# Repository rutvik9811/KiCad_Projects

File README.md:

# KiCad_Projects
These are PCB design Projects ( this doesn't include any code only contains Schematics and PCB design)

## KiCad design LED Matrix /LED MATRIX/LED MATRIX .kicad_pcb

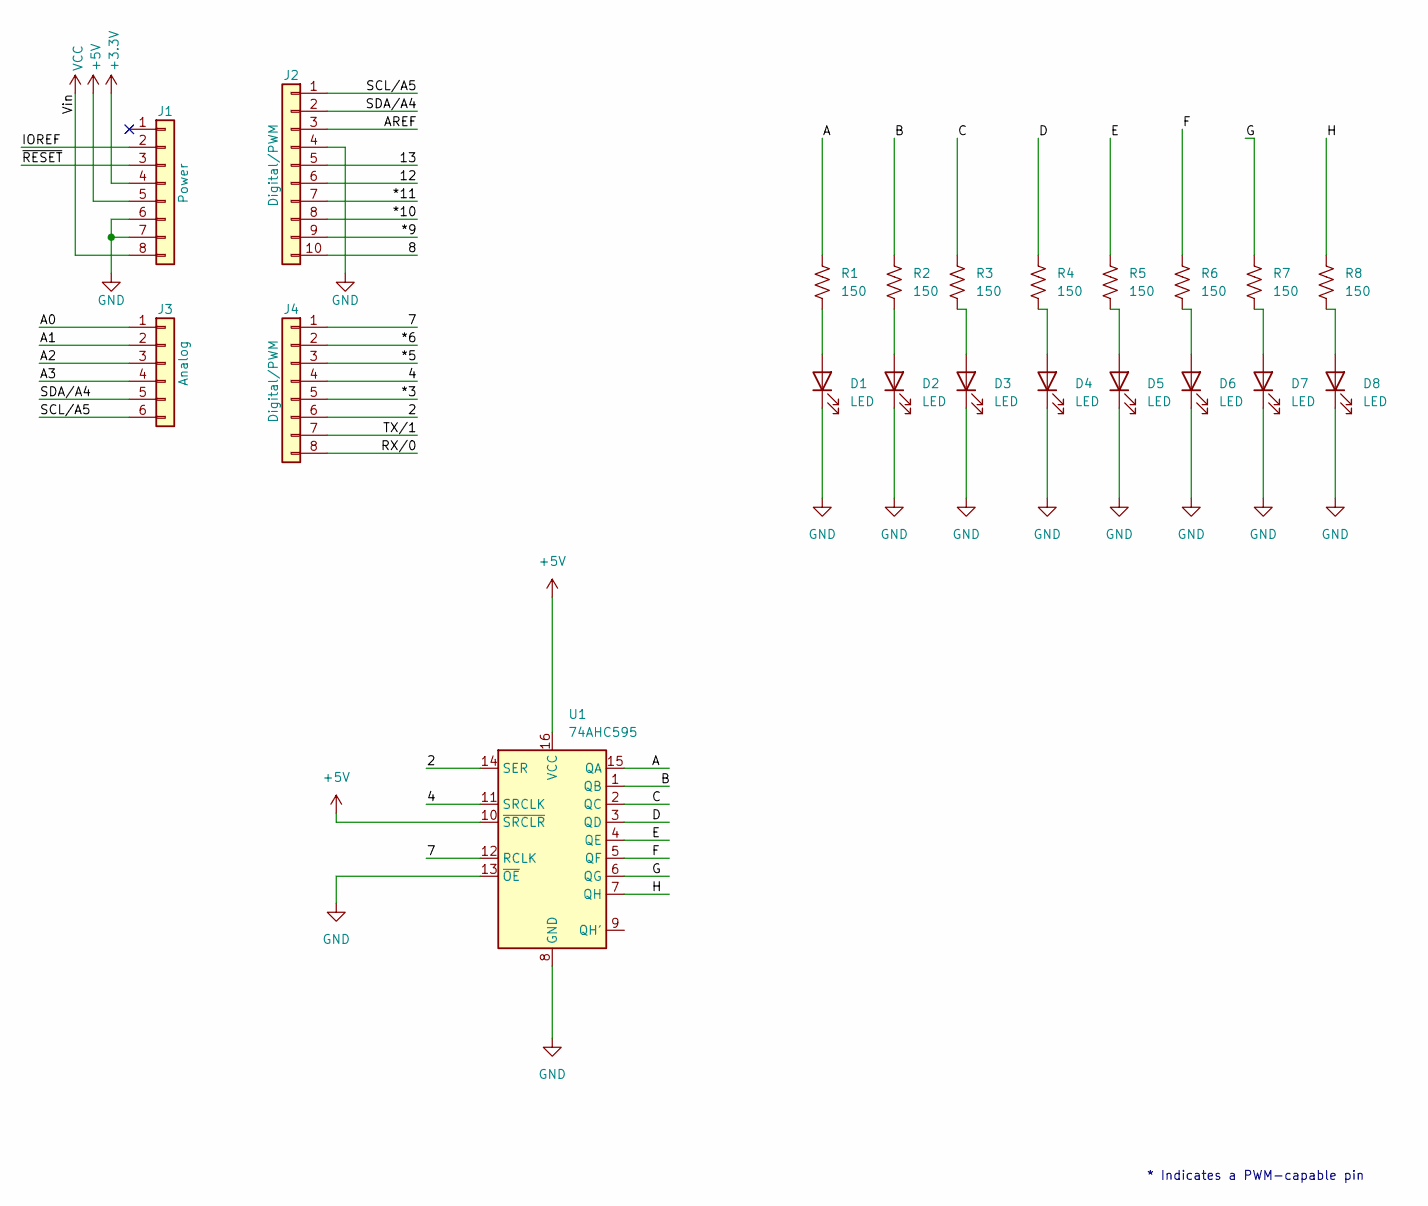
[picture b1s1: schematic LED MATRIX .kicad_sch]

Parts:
D1, D2, D3, D4, D5, D6, D7, D8: LED; LED_D1.8mm_W1.8mm_H2.4mm_Horizontal_O1.27mm_Z1.6mm
J1: Power; PinSocket_1x08_P2.54mm_Vertical
J2: Digital/PWM; PinSocket_1x10_P2.54mm_Vertical
J3: Analog; PinSocket_1x06_P2.54mm_Vertical
J4: Digital/PWM; PinSocket_1x08_P2.54mm_Vertical
R1, R2, R3, R4, R5, R6, R7, R8: 150; R_Axial_DIN0207_L6.3mm_D2.5mm_P10.16mm_Horizontal
U1: 74AHC595; DIP-16_W7.62mm

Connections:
+3V3: J1.4
+5V: J1.5, U1.10 (~SRCLR), U1.16 (VCC)
/2: J4.6, U1.14 (SER)
/4: J4.4, U1.11 (SRCLK)
/7: J4.1, U1.12 (RCLK)
/8: J2.10
/12: J2.6
/13: J2.5
/*3: J4.5
/*5: J4.3
/*6: J4.2
/*9: J2.9
/*10: J2.8
/*11: J2.7
/A: R1.1, U1.15 (QA)
/A0: J3.1
/A1: J3.2
/A2: J3.3
/A3: J3.4
/AREF: J2.3
/B: R2.1, U1.1 (QB)
/C: R3.1, U1.2 (QC)
/D: R4.1, U1.3 (QD)
/E: R5.1, U1.4 (QE)
/F: R6.1, U1.5 (QF)
/G: R7.1, U1.6 (QG)
/H: R8.1, U1.7 (QH)
/IOREF: J1.2
/RX/0: J4.8
/SCL/A5: J2.1, J3.6
/SDA/A4: J2.2, J3.5
/TX/1: J4.7
/~RESET: J1.3
GND: D1.1 (K), D2.1 (K), D3.1 (K), D4.1 (K), D5.1 (K), D6.1 (K), D7.1 (K), D8.1 (K), J1.6, J1.7, J2.4, U1.8 (GND), U1.13 (~OE)
unnamed: D1.2 (A), R1.2
unnamed: D2.2 (A), R2.2
unnamed: D3.2 (A), R3.2
unnamed: D4.2 (A), R4.2
unnamed: D5.2 (A), R5.2
unnamed: D6.2 (A), R6.2
unnamed: D7.2 (A), R7.2
unnamed: D8.2 (A), R8.2
VCC: J1.8

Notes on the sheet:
* Indicates a PWM-capable pin

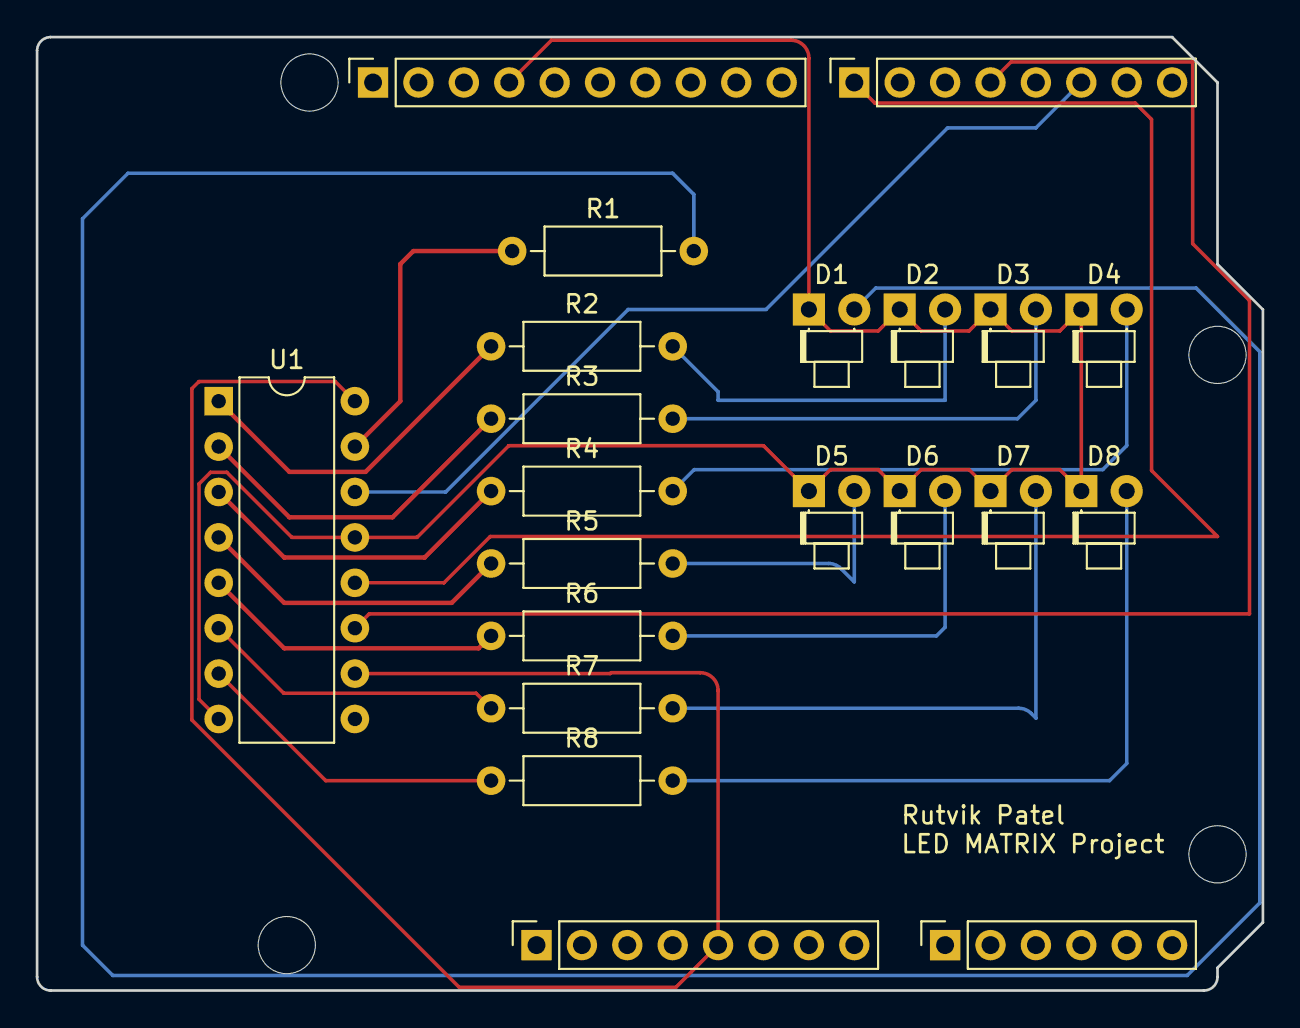
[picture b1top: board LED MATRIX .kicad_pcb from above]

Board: 2 copper layers, 68.6 x 53.3 mm, 25 parts (0 on the bottom side), 23 nets.

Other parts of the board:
MH1, MH2, MH3, MH4: MountingHole_3.2mm

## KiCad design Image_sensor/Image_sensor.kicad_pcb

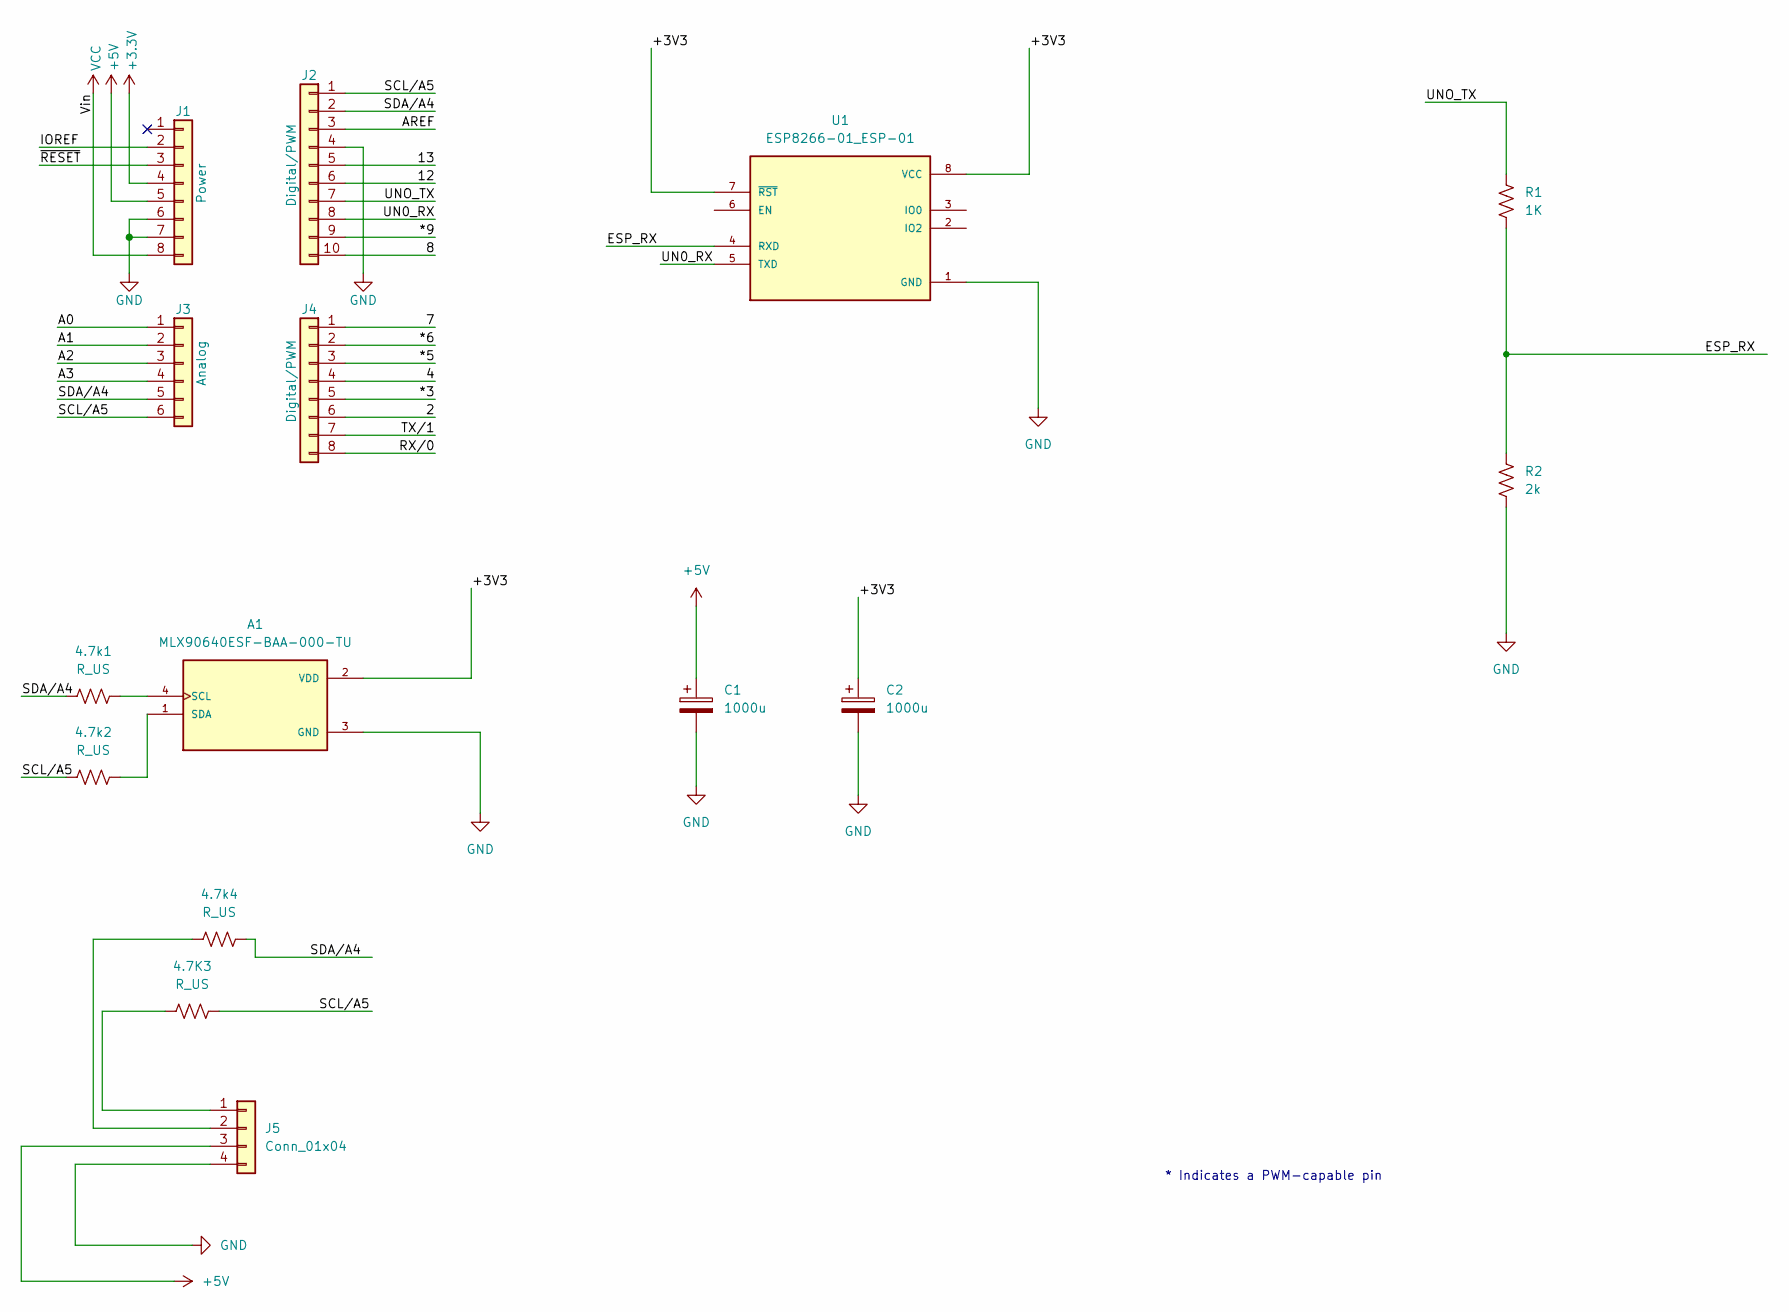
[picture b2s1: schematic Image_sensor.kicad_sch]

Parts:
4.7K3, 4.7k1, 4.7k2, 4.7k4: R_US; R_Axial_DIN0207_L6.3mm_D2.5mm_P10.16mm_Horizontal
A1: MLX90640ESF-BAA-000-TU; TO292P930H600-4; PARTREV 11
C1, C2: 1000u; CP_Radial_D10.0mm_P5.00mm
J1: Power; PinSocket_1x08_P2.54mm_Vertical
J2: Digital/PWM; PinSocket_1x10_P2.54mm_Vertical
J3: Analog; PinSocket_1x06_P2.54mm_Vertical
J4: Digital/PWM; PinSocket_1x08_P2.54mm_Vertical
J5: Conn_01x04; NS-Tech_Grove_1x04_P2mm_Vertical
R1: 1K; R_Axial_DIN0207_L6.3mm_D2.5mm_P10.16mm_Horizontal
R2: 2k; R_Axial_DIN0207_L6.3mm_D2.5mm_P10.16mm_Horizontal
U1: ESP8266-01_ESP-01; XCVR_ESP8266-01_ESP-01; PARTREV V1.2

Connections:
+5V: C1.1, J1.5, J5.3
/2: J4.6
/4: J4.4
/7: J4.1
/8: J2.10
/12: J2.6
/13: J2.5
/*3: J4.5
/*5: J4.3
/*6: J4.2
/*9: J2.9
/A0: J3.1
/A1: J3.2
/A2: J3.3
/A3: J3.4
/AREF: J2.3
/ESP_RX: R1.2, R2.1, U1.4 (RXD)
/IOREF: J1.2
/RX/0: J4.8
/SCL/A5: 4.7K3.2, 4.7k2.1, J2.1, J3.6
/SDA/A4: 4.7k1.1, 4.7k4.2, J2.2, J3.5
/TX/1: J4.7
/UN0_RX: J2.8, U1.5 (TXD)
/UNO_TX: J2.7, R1.1
/~RESET: J1.3
GND: A1.3 (GND), C1.2, C2.2, J1.6, J1.7, J2.4, J5.4, R2.2, U1.1 (GND)
unnamed: 4.7k1.2, A1.4 (SCL)
unnamed: 4.7k2.2, A1.1 (SDA)
unnamed: 4.7K3.1, J5.1
unnamed: 4.7k4.1, J5.2
VCC: J1.8

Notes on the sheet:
* Indicates a PWM-capable pin

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
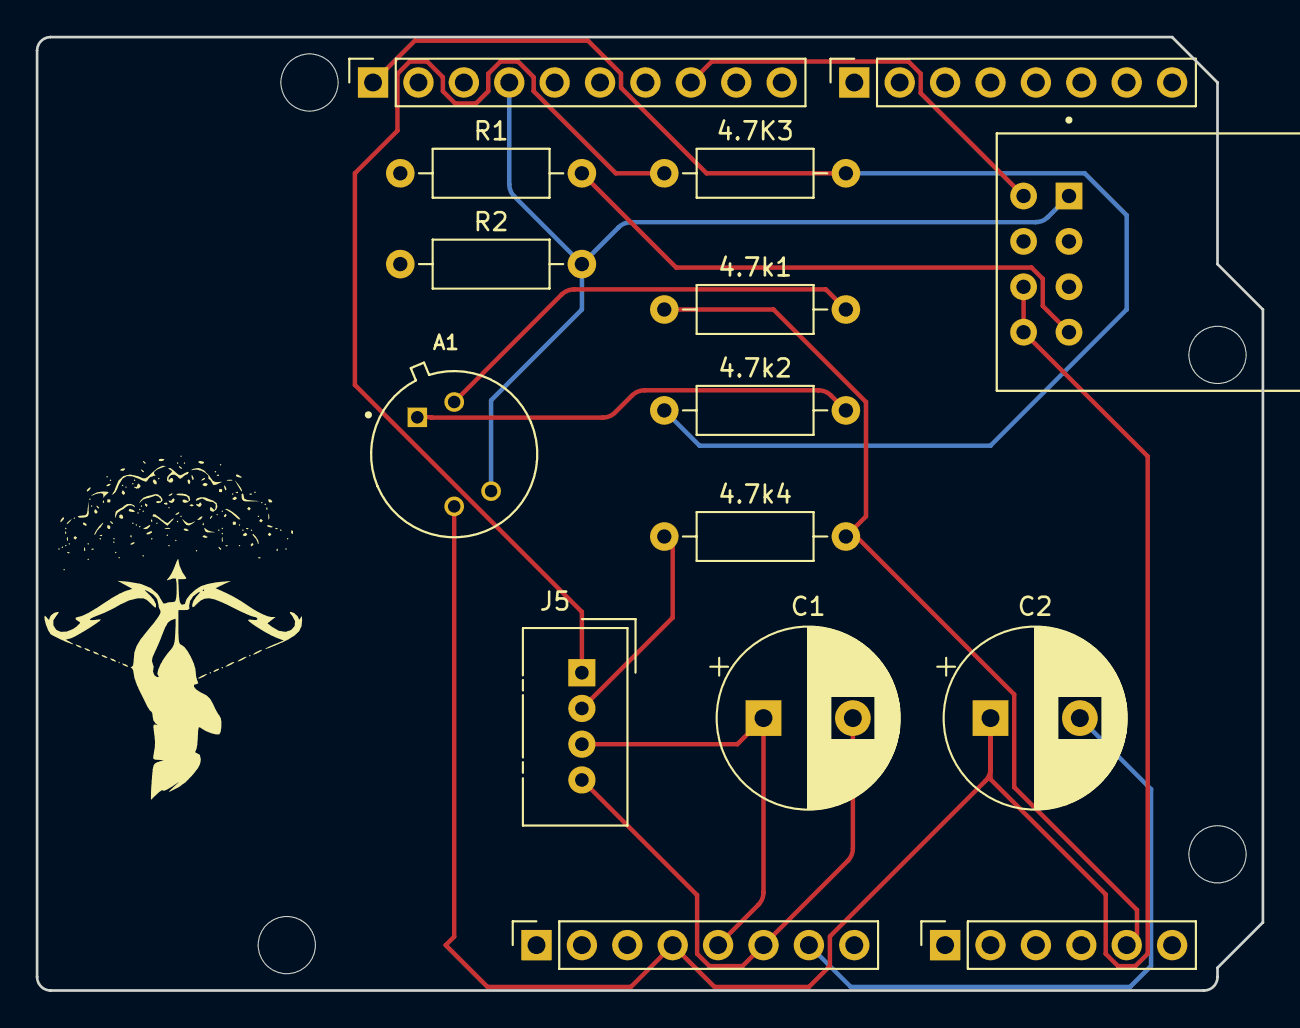
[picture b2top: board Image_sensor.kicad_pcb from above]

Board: 2 copper layers, 68.6 x 53.3 mm, 19 parts (0 on the bottom side), 12 nets.

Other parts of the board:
MH1, MH2, MH3, MH4: MountingHole_3.2mm

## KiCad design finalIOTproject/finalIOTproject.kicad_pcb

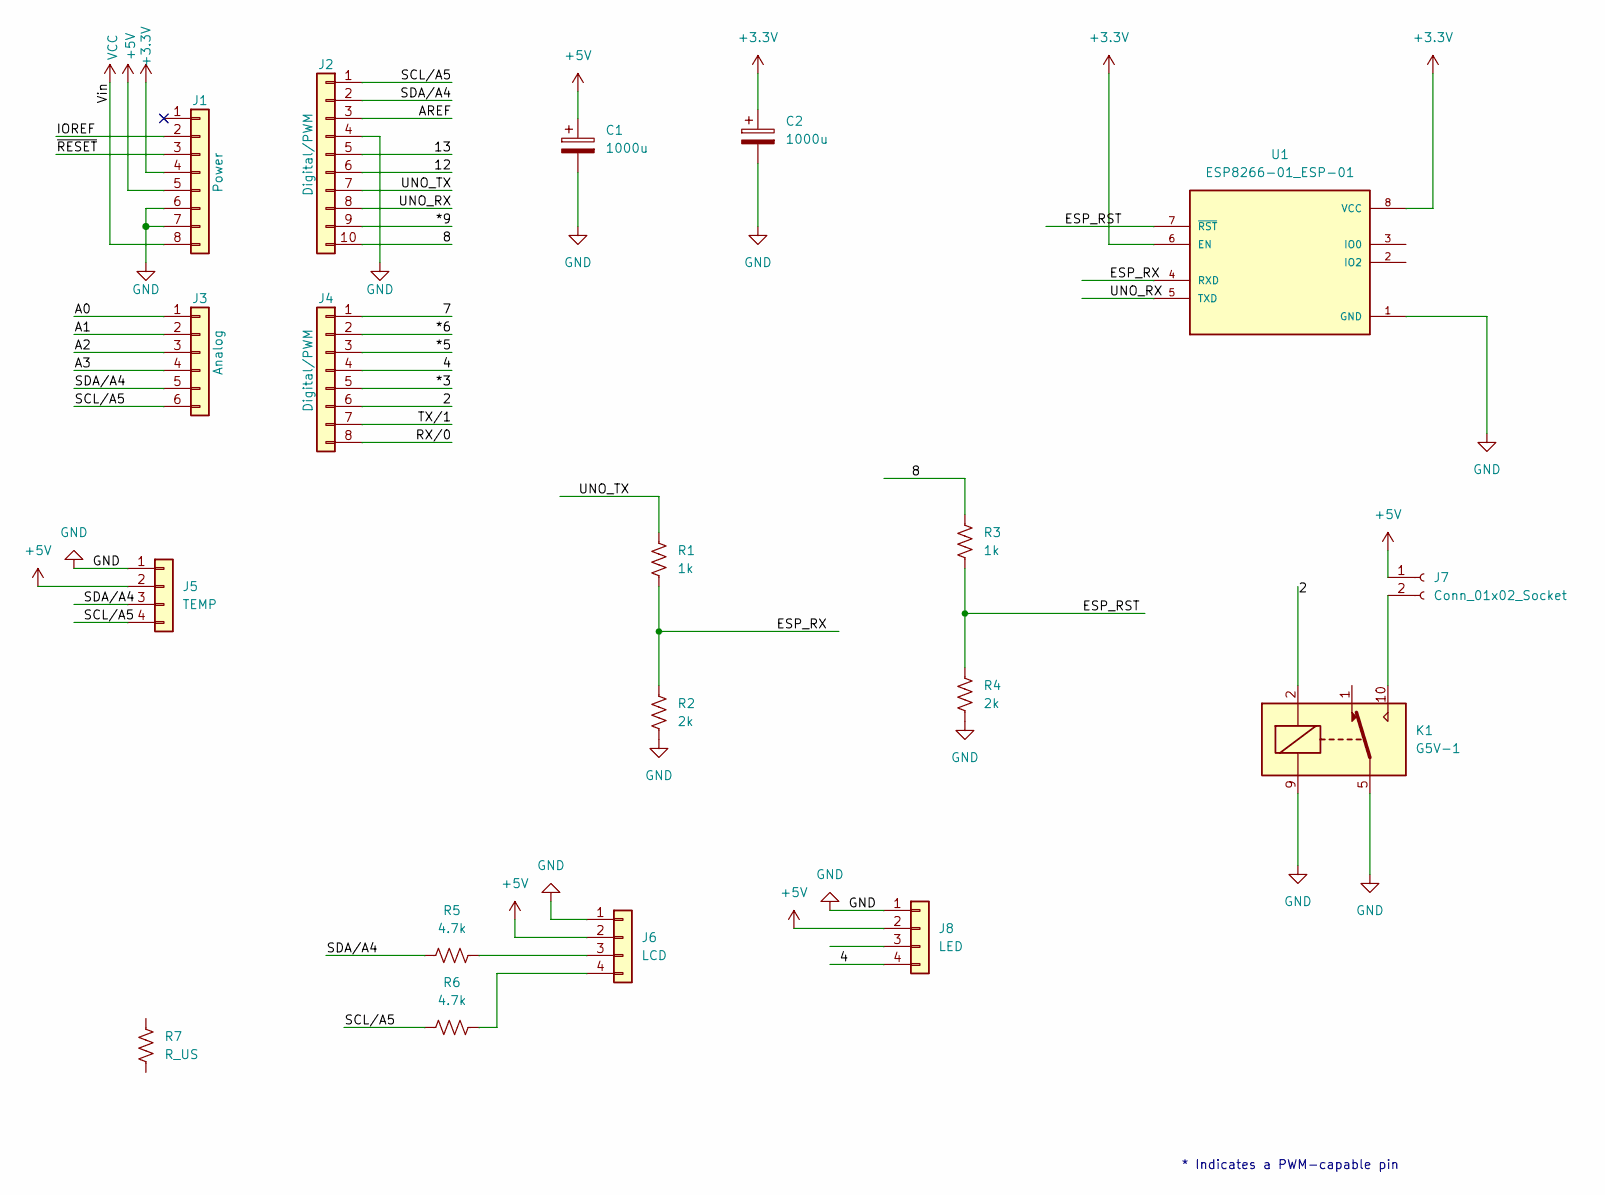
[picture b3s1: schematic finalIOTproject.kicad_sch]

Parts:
C1, C2: 1000u; CP_Radial_D10.0mm_P5.00mm
J1: Power; PinSocket_1x08_P2.54mm_Vertical
J2: Digital/PWM; PinSocket_1x10_P2.54mm_Vertical
J3: Analog; PinSocket_1x06_P2.54mm_Vertical
J4: Digital/PWM; PinSocket_1x08_P2.54mm_Vertical
J5: TEMP; NS-Tech_Grove_1x04_P2mm_Vertical
J6: LCD; NS-Tech_Grove_1x04_P2mm_Vertical
J7: Conn_01x02_Socket; PinHeader_1x02_P2.54mm_Vertical
J8: LED; NS-Tech_Grove_1x04_P2mm_Vertical
K1: G5V-1; Relay_SPDT_Omron_G5V-1
R1, R3: 1k; R_Axial_DIN0207_L6.3mm_D2.5mm_P10.16mm_Horizontal
R2, R4: 2k; R_Axial_DIN0207_L6.3mm_D2.5mm_P10.16mm_Horizontal
R5, R6: 4.7k; R_Axial_DIN0207_L6.3mm_D2.5mm_P10.16mm_Horizontal
R7: R_US; R_Axial_DIN0207_L6.3mm_D2.5mm_P10.16mm_Horizontal
U1: ESP8266-01_ESP-01; XCVR_ESP8266-01_ESP-01; PARTREV V1.2

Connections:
+3.3V: C2.1, J1.4, U1.6 (EN), U1.8 (VCC)
+5V: C1.1, J1.5, J5.2, J6.2, J7.1, J8.2
/2: J4.6, K1.2
/4: J4.4, J8.4
/7: J4.1
/8: J2.10, R3.1
/12: J2.6
/13: J2.5
/*3: J4.5
/*5: J4.3
/*6: J4.2
/*9: J2.9
/A0: J3.1
/A1: J3.2
/A2: J3.3
/A3: J3.4
/AREF: J2.3
/ESP_RST: R3.2, R4.1, U1.7 (~RST)
/ESP_RX: R1.2, R2.1, U1.4 (RXD)
/IOREF: J1.2
/RX/0: J4.8
/SCL/A5: J2.1, J3.6, J5.4, R6.1
/SDA/A4: J2.2, J3.5, J5.3, R5.1
/TX/1: J4.7
/UNO_RX: J2.8, U1.5 (TXD)
/UNO_TX: J2.7, R1.1
/~RESET: J1.3
GND: C1.2, C2.2, J1.6, J1.7, J2.4, J5.1, J6.1, J8.1, K1.5, K1.6, K1.9, R2.2, R4.2, U1.1 (GND)
unnamed: J6.3, R5.2
unnamed: J6.4, R6.2
unnamed: J7.2, K1.10
VCC: J1.8

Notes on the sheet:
* Indicates a PWM-capable pin

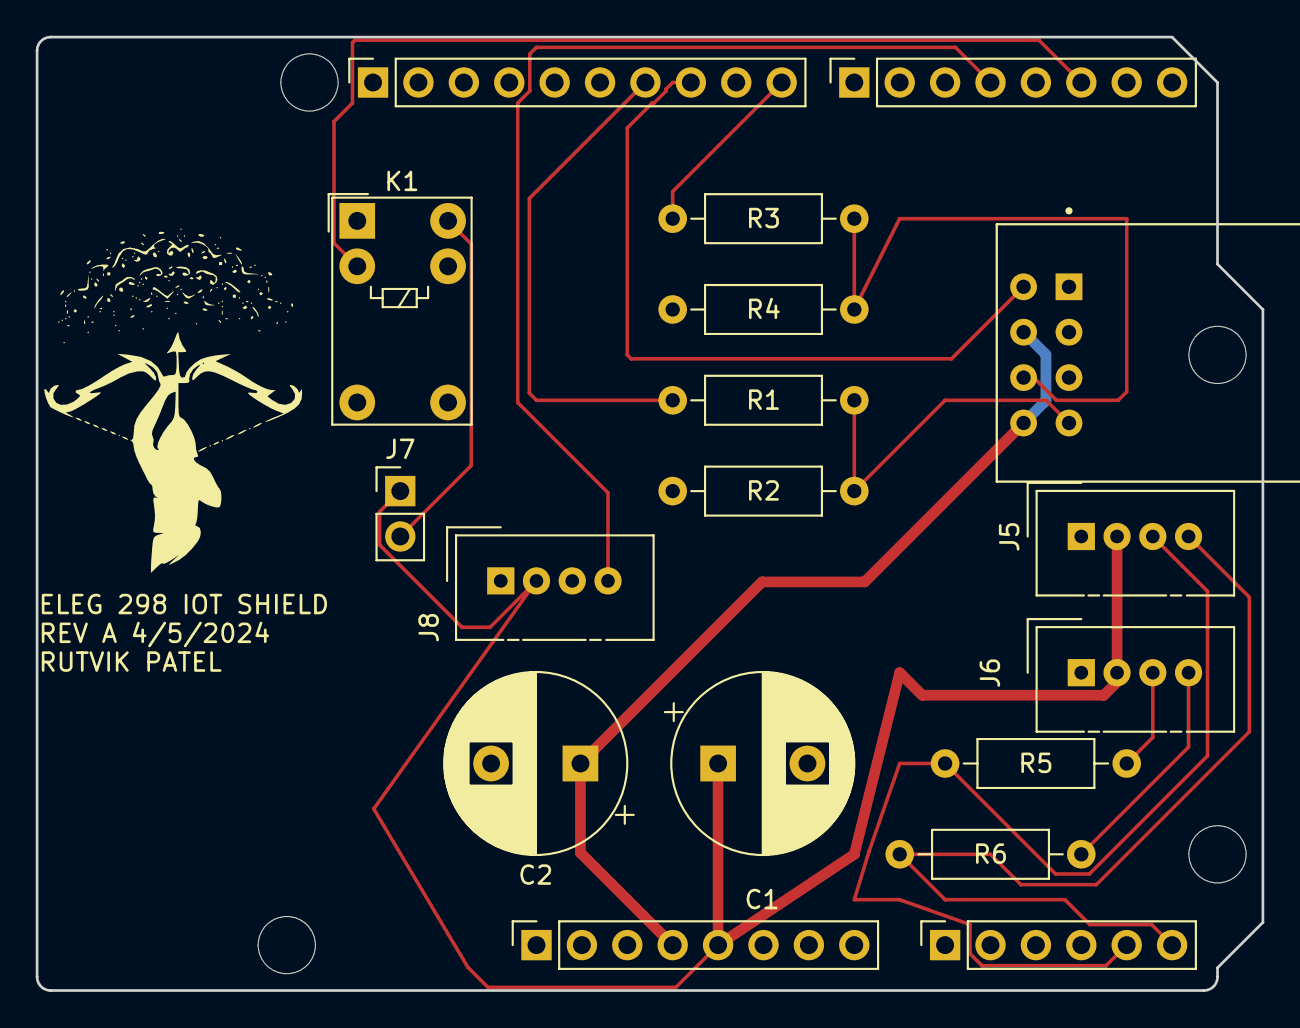
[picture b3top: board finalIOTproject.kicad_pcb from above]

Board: 2 copper layers, 68.6 x 53.3 mm, 22 parts (0 on the bottom side), 15 nets.

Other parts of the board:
MH1, MH2, MH3, MH4: MountingHole_3.2mm

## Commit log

2024-05-31 Add files via upload
    This is an IOT project which sense temperature and send data to ADAfruit via ESP
2024-05-31 Add files via upload
    This is the project where thermal image sensor is used to sense the Images and display on the grove LED 0.96
2024-05-31 Introduction
2024-06-04 Create Project Description
